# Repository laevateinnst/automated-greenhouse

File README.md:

# EMBEDDED SYSTEMS BSCpE - 4B "AUTOMATED-GREENHOUSE"

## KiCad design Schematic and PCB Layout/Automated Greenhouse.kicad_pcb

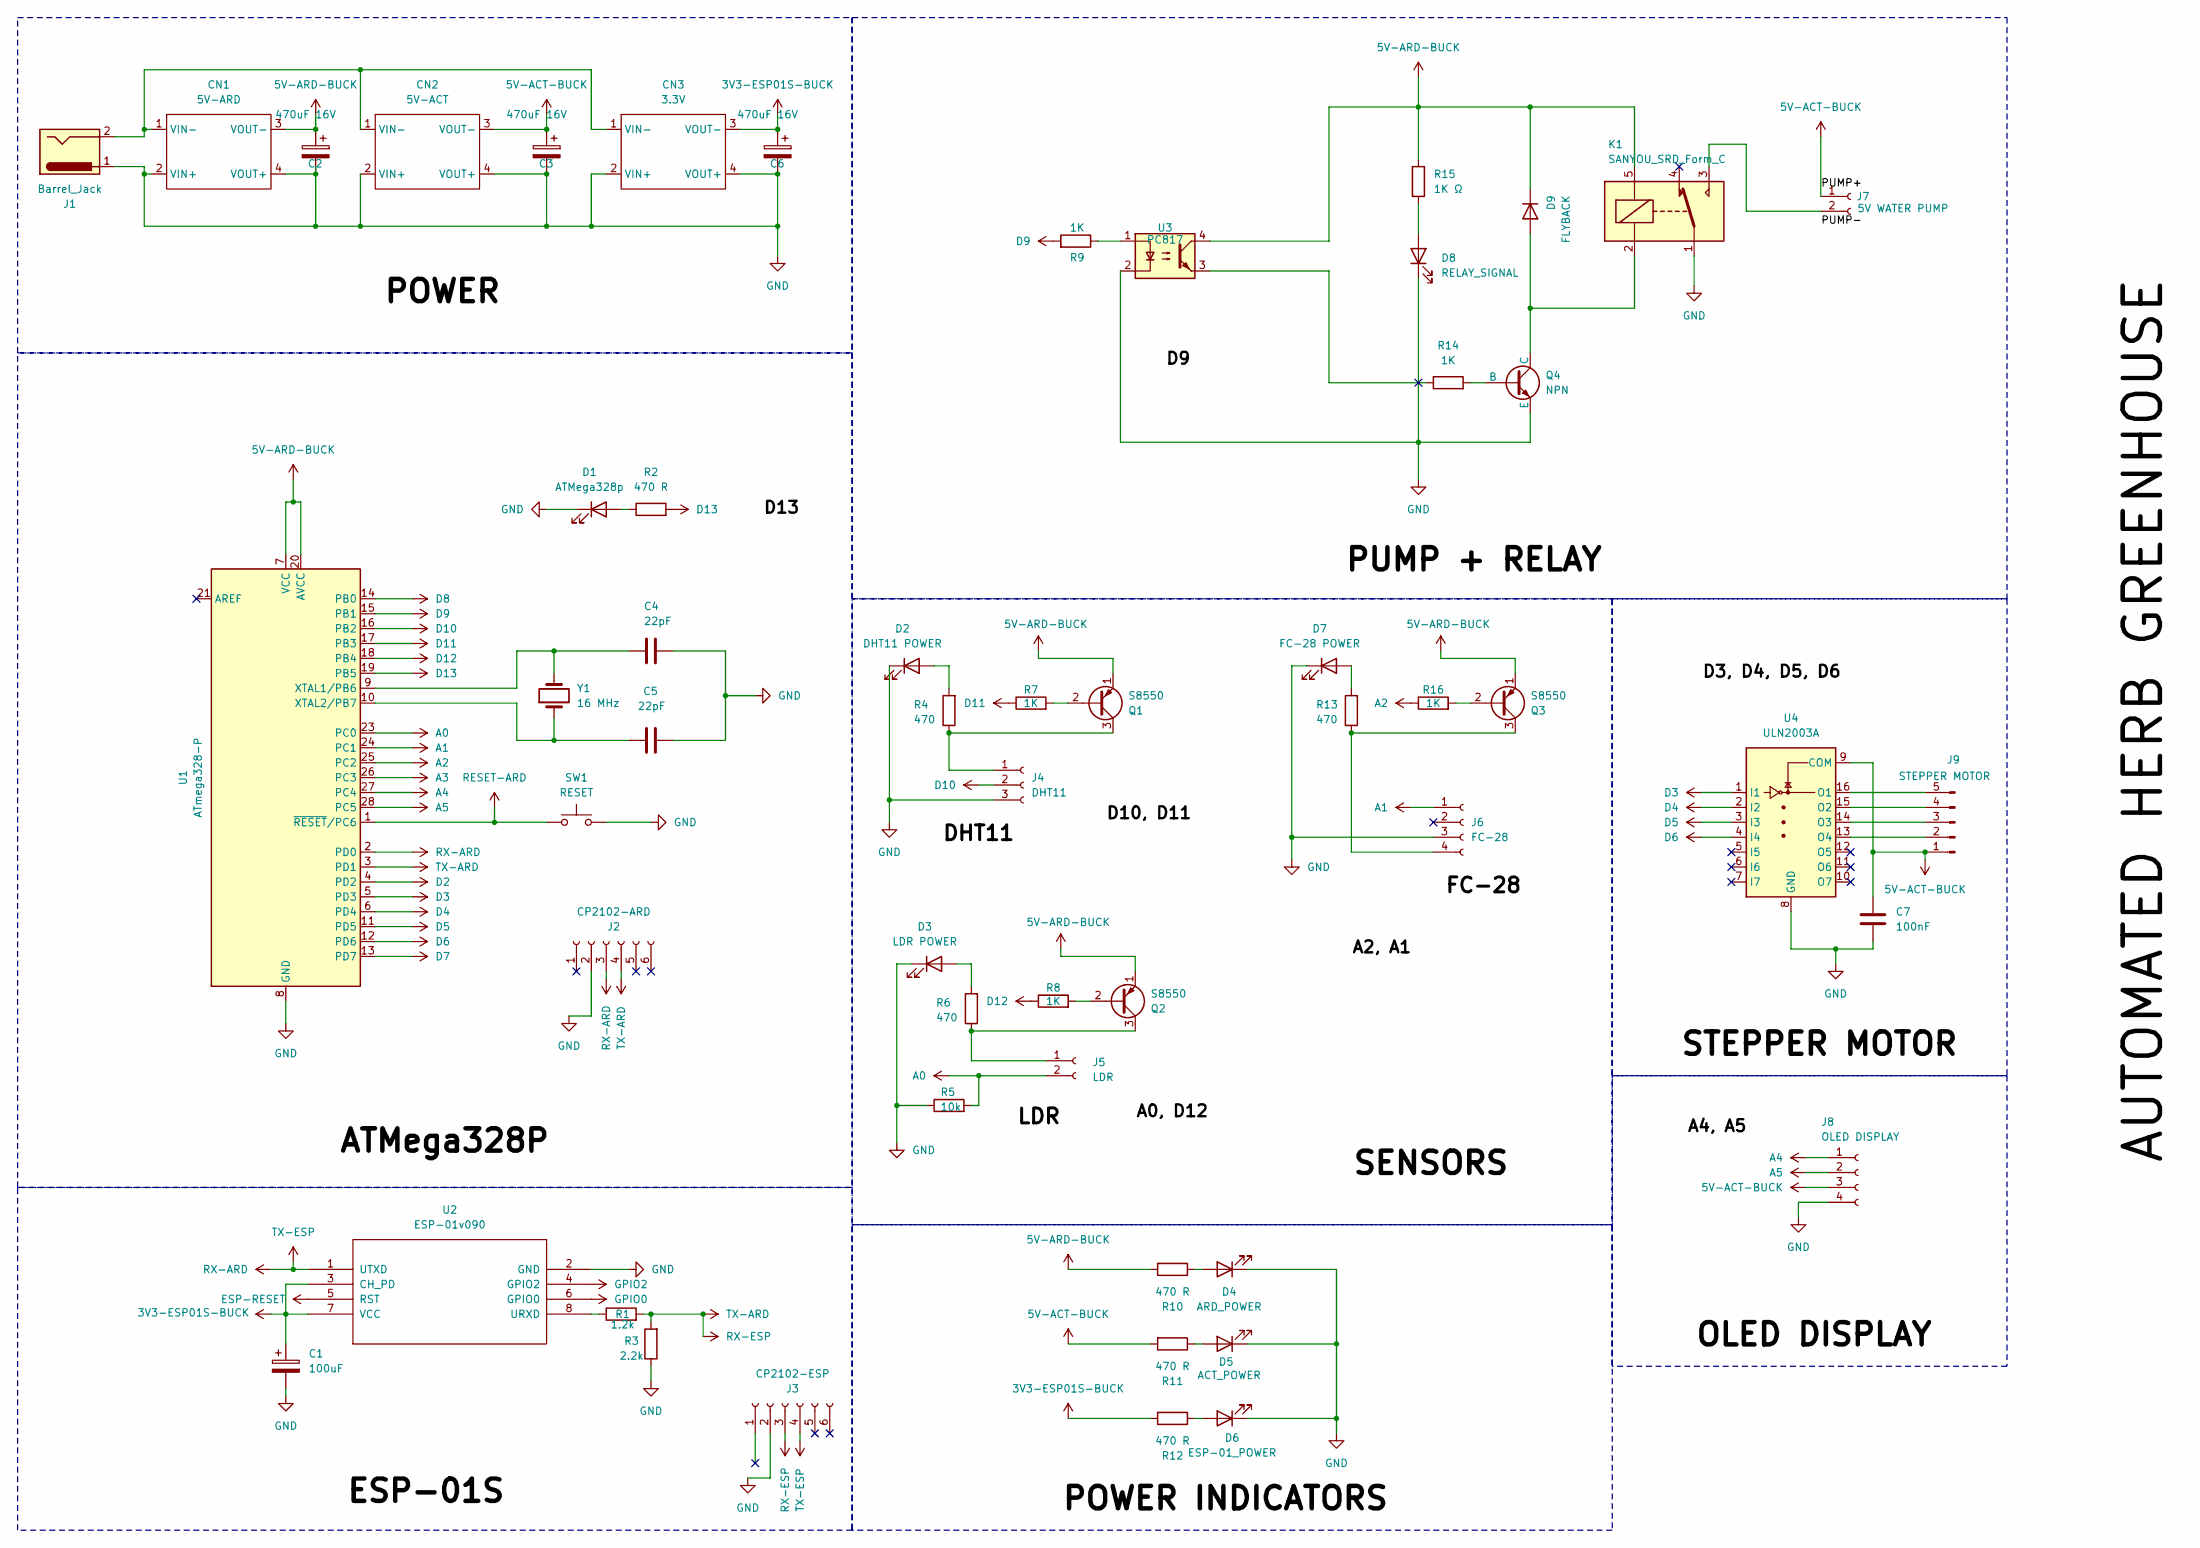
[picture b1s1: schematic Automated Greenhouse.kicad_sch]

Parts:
C1: 100uF; CP_Radial_D5.0mm_P2.00mm
C2, C3, C6: 470uF 16V; CP_Radial_D6.3mm_P2.50mm
C4, C5: 22pF; C_Disc_D4.3mm_W1.9mm_P5.00mm
C7: 100nF; C_Disc_D5.1mm_W3.2mm_P5.00mm
CN1: 5V-ARD; Mini_Buck_DCDC
CN2: 5V-ACT; Mini_Buck_DCDC
CN3: 3.3V; Mini_Buck_DCDC
D1: ATMega328p; LED_D3.0mm
D2: DHT11 POWER; LED_D3.0mm
D3: LDR POWER; LED_D3.0mm
D4: ARD_POWER; LED_D3.0mm
D5: ACT_POWER; LED_D3.0mm
D6: ESP-01_POWER; LED_D3.0mm
D7: FC-28 POWER; LED_D3.0mm
D8: RELAY_SIGNAL; LED_D3.0mm
D9: FLYBACK; D_DO-41_SOD81_P7.62mm_Horizontal
J1: Barrel_Jack; BarrelJack_Horizontal
J2: CP2102-ARD; PinSocket_1x06_P2.54mm_Vertical
J3: CP2102-ESP; PinSocket_1x06_P2.54mm_Vertical
J4: DHT11; JST_EH_B3B-EH-A_1x03_P2.50mm_Vertical
J5: LDR; JST_EH_B2B-EH-A_1x02_P2.50mm_Vertical
J6: FC-28; JST_EH_B4B-EH-A_1x04_P2.50mm_Vertical
J7: 5V WATER PUMP; JST_EH_B2B-EH-A_1x02_P2.50mm_Vertical
J8: OLED DISPLAY; JST_EH_B4B-EH-A_1x04_P2.50mm_Vertical
J9: STEPPER MOTOR; JST_EH_B5B-EH-A_1x05_P2.50mm_Vertical
K1: SANYOU_SRD_Form_C; Relay_SPDT_SANYOU_SRD_Series_Form_C
Q1, Q2, Q3: S8550; TO-92_Inline
Q4: NPN; TO-92_Inline_Wide
R1: 1.2k; R_Axial_DIN0207_L6.3mm_D2.5mm_P7.62mm_Horizontal
R2, R10, R11, R12: 470 R; R_Axial_DIN0207_L6.3mm_D2.5mm_P7.62mm_Horizontal
R3: 2.2k; R_Axial_DIN0207_L6.3mm_D2.5mm_P7.62mm_Horizontal
R4, R6, R13: 470; R_Axial_DIN0207_L6.3mm_D2.5mm_P7.62mm_Horizontal
R5: 10k; R_Axial_DIN0207_L6.3mm_D2.5mm_P7.62mm_Horizontal
R7, R8, R14, R16: 1K; R_Axial_DIN0207_L6.3mm_D2.5mm_P7.62mm_Horizontal
R9: 1K; R_Axial_DIN0207_L6.3mm_D2.5mm_P10.16mm_Horizontal
R15: 1K Ω; R_Axial_DIN0207_L6.3mm_D2.5mm_P7.62mm_Horizontal
SW1: RESET; SW_PUSH_6mm
U1: ATmega328-P; DIP-28_W7.62mm
U2: ESP-01v090; ESP-01
U3: PC817; DIP-4_W7.62mm
U4: ULN2003A; DIP-16_W7.62mm_LongPads
Y1: 16 MHz; Crystal_HC49-4H_Vertical

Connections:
3V3-ESP01S-BUCK: C1.1, C6.1, CN3.3 (VOUT-), R12.2, U2.3 (CH_PD), U2.7 (VCC)
5V-ACT-BUCK: C3.1, C7.1, CN2.3 (VOUT-), J7.1, J8.3, J9.1, R11.2, U4.9 (COM); also elsewhere on the board
5V-ARD-BUCK: C2.1, CN1.3 (VOUT-), D9.1 (K), K1.5, Q1.1 (E), Q2.1 (E), Q3.1 (E), R10.2, R15.1, U1.7 (VCC), U1.20 (AVCC), U3.4; also elsewhere on the board
A0: J5.2, R5.2, U1.23 (PC0)
A1: J6.1, U1.24 (PC1)
A2: R16.1, U1.25 (PC2)
A3: U1.26 (PC3)
A4: J8.1, U1.27 (PC4)
A5: J8.2, U1.28 (PC5)
D2: U1.4 (PD2)
D3: U1.5 (PD3), U4.1 (I1)
D4: U1.6 (PD4), U4.2 (I2)
D5: U1.11 (PD5), U4.3 (I3)
D6: U1.12 (PD6), U4.4 (I4)
D7: U1.13 (PD7)
D8: U1.14 (PB0)
D9: R9.2, U1.15 (PB1)
D10: J4.2, U1.16 (PB2)
D11: R7.1, U1.17 (PB3)
D12: R8.1, U1.18 (PB4)
D13: R2.2, U1.19 (PB5)
ESP-RESET: U2.5 (RST)
GND: C1.2, C2.2, C3.2, C4.1, C5.2, C6.2, C7.2, CN1.2 (VIN+), CN1.4 (VOUT+), CN2.2 (VIN+), CN2.4 (VOUT+), CN3.2 (VIN+), CN3.4 (VOUT+), D1.1 (K), D2.1 (K), D3.1 (K), D4.1 (K), D5.1 (K), D6.1 (K), D7.1 (K), D8.1 (K), J1.1, J2.2, J3.2, J4.3, J6.3, J8.4, K1.1, Q4.3 (E), R3.1, R5.1, SW1.2, U1.8 (GND), U1.22 (GND), U2.2 (GND), U3.2, U4.8 (GND); also elsewhere on the board
GPIO0: U2.6 (GPIO0)
GPIO2: U2.4 (GPIO2)
unnamed: CN1.1 (VIN-), CN2.1 (VIN-), CN3.1 (VIN-), J1.2
unnamed: D1.2 (A), R2.1
unnamed: D2.2 (A), R4.2
unnamed: D3.2 (A), R6.2
unnamed: D4.2 (A), R10.1
unnamed: D5.2 (A), R11.1
unnamed: D6.2 (A), R12.1
unnamed: D7.2 (A), R13.2
unnamed: D8.2 (A), R15.2
unnamed: D9.2 (A), K1.2, Q4.1 (C)
unnamed: J4.1, Q1.3 (C), R4.1
unnamed: J5.1, Q2.3 (C), R6.1
unnamed: J6.4, Q3.3 (C), R13.1
unnamed: J7.2, K1.3
unnamed: J9.2, U4.13 (O4)
unnamed: J9.3, U4.14 (O3)
unnamed: J9.4, U4.15 (O2)
unnamed: J9.5, U4.16 (O1)
unnamed: Q1.2 (B), R7.2
unnamed: Q2.2 (B), R8.2
unnamed: Q3.2 (B), R16.2
unnamed: Q4.2 (B), R14.2
unnamed: R9.1, U3.1
unnamed: R14.1, U3.3
unnamed: C4.2, U1.9 (XTAL1/PB6), Y1.2
unnamed: C5.1, U1.10 (XTAL2/PB7), Y1.1
unnamed: R1.1, U2.8 (URXD)
RESET-ARD: SW1.1, U1.1 (~RESET/PC6)
RX-ARD: J2.3, J3.4, U1.2 (PD0), U2.1 (UTXD)
RX-ESP: J2.4, J3.3, R1.2, R3.2, U1.3 (PD1)

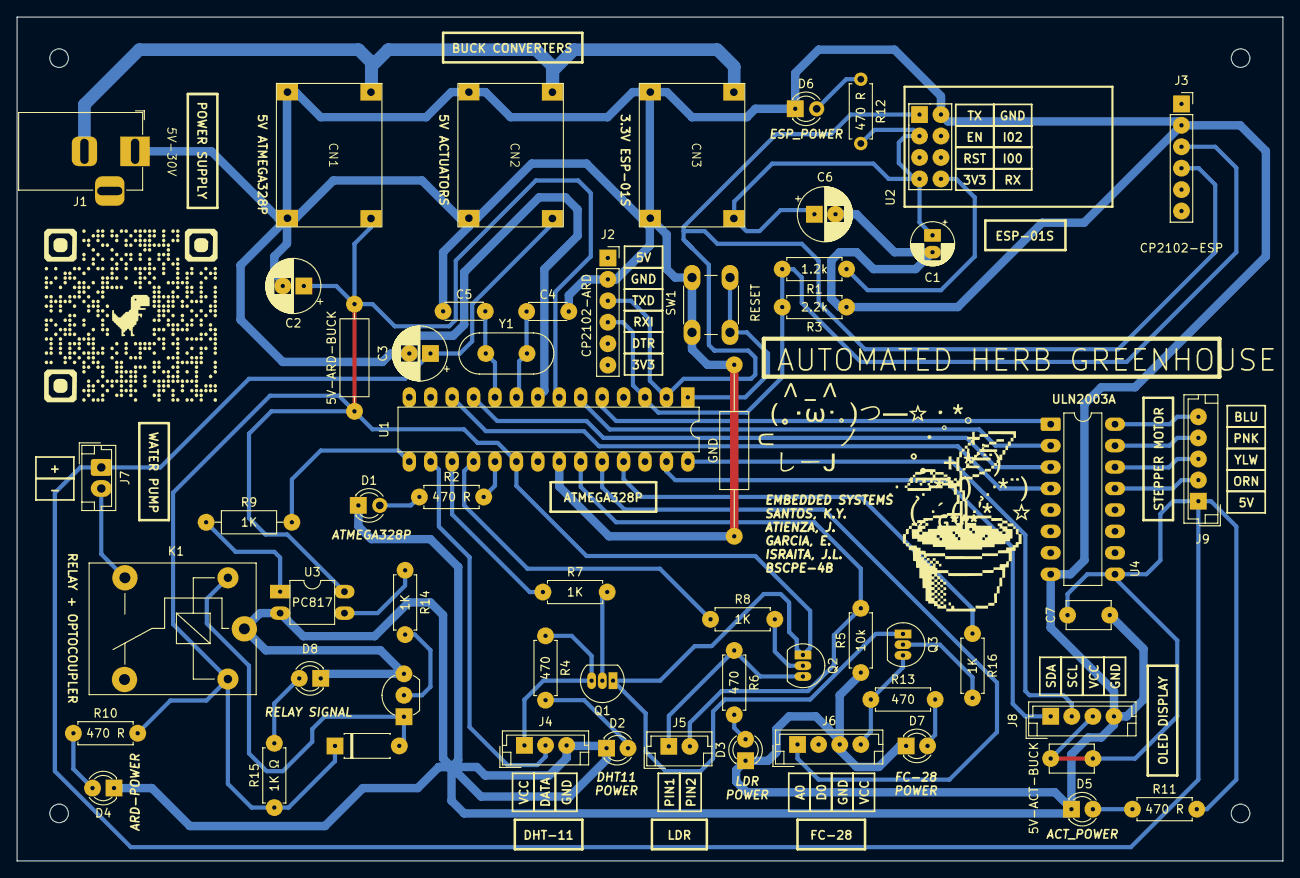
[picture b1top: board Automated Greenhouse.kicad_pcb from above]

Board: 2 copper layers, 150.0 x 100.0 mm, 58 parts (0 on the bottom side), 48 nets.

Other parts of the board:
5V-ACT-BUCK: C_Disc_D5.1mm_W3.2mm_P5.00mm
5V-ARD-BUCK: R; R_Axial_DIN0309_L9.0mm_D3.2mm_P12.70mm_Horizontal
GND: R; R_Axial_DIN0309_L9.0mm_D3.2mm_P20.32mm_Horizontal

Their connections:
5V-ACT-BUCK: 5V-ACT-BUCK.1, 5V-ACT-BUCK.2; also elsewhere on the board
5V-ARD-BUCK: 5V-ARD-BUCK.1, 5V-ARD-BUCK.2; also elsewhere on the board
GND: GND.1, GND.2; also elsewhere on the board

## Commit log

2025-12-08 Front_End
2025-12-08 Arduino
2025-12-08 README.md
2025-12-10 Back_End
2025-12-11 Code
2025-12-11 Upload KiCAD files
2025-12-11 Manalangin
2025-12-14 Final Output
2025-12-15 deleted
2025-12-15 final code
2025-12-15 finalcode
